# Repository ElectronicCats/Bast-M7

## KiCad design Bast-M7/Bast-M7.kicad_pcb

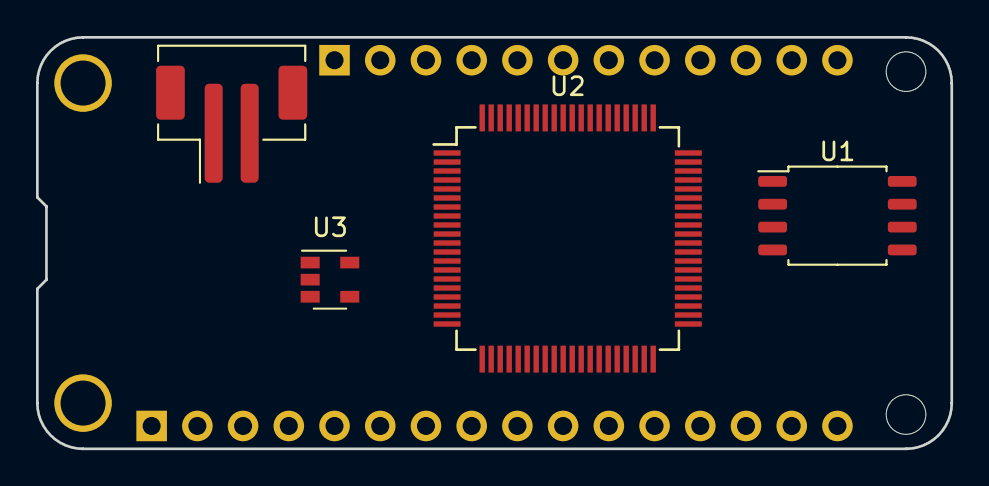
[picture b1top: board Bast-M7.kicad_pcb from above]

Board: 2 copper layers, 50.8 x 22.9 mm, 6 parts (0 on the bottom side), 28 nets, no tracks yet.

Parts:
J1: Conn_Battery; JST_PH_B2B-PH-SM4-TB_1x02-1MP_P2.00mm_Vertical
J3: Conn_Left; PinSocket_1x16_P2.54mm_Vertical
J4: Conn_Right; PinSocket_1x12_P2.54mm_Vertical
U1: W25Q128JVS; SOIC-8_5.23x5.23mm_P1.27mm
U2: MIMXRT1011DAE5A; TQFP-80_12x12mm_P0.5mm
U3: AP2112K-3.3; SOT-23-5

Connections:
+3V3: J3.2, U1.8, U2.7, U2.17, U2.18, U2.42, U2.50, U2.63, U2.71
+BATT: J1.2, J4.1
/A0: J3.5, U2.59
/A1: J3.6, U2.52
/A2: J3.7, U2.51
/A3: J3.8, U2.49
/A4: J3.9, U2.48
/A5: J3.10, U2.47
/DCDC_OUT: U2.14, U2.53, U2.77
/FlexSPI_CLK_A: U1.6, U2.65
/FlexSPI_D0_A: U1.5, U2.66
/FlexSPI_D1_A: U1.2, U2.68
/FlexSPI_D2_A: U1.3, U2.67
/FlexSPI_D3_A: U1.7, U2.64
/FlexSPI_SS0: U1.1, U2.69
/GPIO10: J4.7, U2.2
/GPIO11: J4.6, U2.1
/GPIO12: J4.5, U2.80
/GPIO13: J4.4, U2.79
/MISO: J3.13, U2.58
/MOSI: J3.12, U2.57
/RX: J3.14, U2.10
/SCK: J3.11, U2.55
/SCL: J4.11, U2.11
/SDA: J4.12, U2.12
/TX: J3.15, U2.9
GND: J1.1, J3.4, U1.4, U2.16, U2.20, U2.23, U2.30, U2.34, U2.41, U2.54, U2.78
unnamed: U2.15, U2.19

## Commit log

2020-03-22 Initi Schematic
2020-03-22 USB pins
2020-04-19 Update SPI Flash, GPIOs, Analog pins, SPI, I2C and Serial
2020-04-19 Add format feather
2020-04-19 Charger battery, fix Serial, and Boot pins
2020-07-28 boot, swconn and another connections added
2020-07-29 boot fixed
2020-07-31 nvcc and some capacitors fixed
2020-07-31 fixed some pin configurations and capacitors
2020-08-03 reset and other changes
2020-08-03 boot label fixed
